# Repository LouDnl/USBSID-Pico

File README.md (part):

<br>
# 
USBSID-Pico is a RaspberryPi Pico/PicoW (RP2040) & Pico2/Pico2W (RP2350) based board for interfacing one or two MOS SID chips and/or hardware SID emulators over (WEB)USB with your computer, phone, ASID supporting player or USB midi controller.  

# This is USBSID-Pico! :)
| **“Raster Bar” (8-bit)** | **Van Halen's Jump<br>dual SID in Stereo!** | **Next Level** | **Outerversal<br>dual SID in Stereo!** |
|:-:|:-:|:-:|:-:|
| <br><small><sub>by LukHash</sub></small> | <br><small><sub>by Nordischsound</sub></small> | <br><small><sub>by Performers</sub> | <br><small><sub>by Abyxus</sub></small> |

| **Wonderland XI** | **Wonderland XII** | **Wonderland XIII** | **Wonderland XIV** |
|:-:|:-:|:-:|:-:|
| <br><small><sub>by Censor Design</sub></small> | <br><small><sub>by Censor Design</sub></small> | <br><small><sub>by Censor Design</sub> | <br><small><sub>by Censor Design</sub></small> |

# USBSID-Pro (Soon™)
In development is a modular USBSID-Pro featuring 4 SID sockets with 4 mono out ports, switchable audio channels into a single stereo out jack , Midi port, an onboard rp2350b and more. No release date has been planned yet!

# Index
* [This is USBSID-Pico! :)](#this-is-usbsid-pico-)
* [Swag!](#swag)
* [Software support & Features](#software-support-and-features)
  * [USBSID-Configtool](#usbsid-configtool)
  * [Software manual](doc/USBSID-Pico-software-manual.adoc) [PDF](doc/USBSID-Pico-software-manual.pdf)
  * [SID files](#sid-files)
    - [Webbased SID players](#webbased-sid-players)
    - [SID players](#sid-players)
    - [Amiga SID players](#amiga-sid-players)
  * [Commodore 64 emulators](#commodore-64-emulators)
  * [Chiptune trackers using SID's](#chiptune-trackers-using-sids)
  * [Driver code](#driver-code)
  * [Midi](#midi)
  * [Cynthcart VST](#cynthcart-vst)
* [Questions & Support](#questions-and-support)
* [Known issues](#known-issues)
* [Project status](#project-status)
  * [Code status](#code-status)
  * [Supported platforms](#supported-platforms)
  * [Linux Udev rules](#linux-udev-rules)
  * [Windows driver](#windows-driver)
* [Firmware](#firmware)
  * [Configuring your board's firmware](#configuring-your-boards-firmware)
    * [Testing your board](#testing-your-board)
  * [Firmware features](#firmware-features)
    * [Embedded Cynthcart](doc/USBSID-Pico-Cynthcart-manual.adoc) [(PDF)](doc/USBSID-Pico-Cynthcart-manual.pdf)
    * [Embedded USBSID-Player](doc/USBSID-Player-manual.adoc) [(PDF)](doc/USBSID-Player-manual.pdf)
  * [Firmware types and naming](doc/USBSID-Pico-firmware-manual.adoc) [(PDF)](doc/USBSID-Pico-firmware-manual.pdf)
  * [How to flash new firmware](doc/USBSID-Pico-firmware-manual.adoc) [(PDF)](doc/USBSID-Pico-firmware-manual.pdf)
  * [How to configure your board](doc/USBSID-Pico-firmware-manual.adoc) [(PDF)](doc/USBSID-Pico-firmware-manual.pdf)
  * [Building](#building)
* [Hardware](#hardware)
  * [Volume board](#volume-board)
  * [Where to buy](#where-to-buy)
  * [PCB usage information](#pcb-usage-information)
    * [PCB revision v1.0 manual](#pcb-revision-v10-manual)
    * [PCB revision v1.3 manual](#pcb-revision-v13-manual)
  * [Cases](#cases)
  * [PCB Features](#pcb-features)
  * [Open source design files, schematic and BOM](#open-source-design-files-schematic-and-bom)
  * [PCB Development](#pcb-development)
* [Examples](#examples)
* [Acknowledgements](#acknowledgements)
* [Disclaimer](#disclaimer)
* [License](#license)
* [Certification](#certification)

# Swag!
Do you like swag!? Yes please!! [greyandslate](https://bsky.app/profile/greyandslate.bsky.social) created these great t-shirt designs which are available for purchase in his [Smallrun shop](https://smallrun.net/shop/grey-and-slate-haberdashers), link below.  
**Use coupon code USBSID15 for a 15% discount!**  

# Software support and features
  
See the [Software manual](doc/USBSID-Pico-software-manual.adoc) for more information on how to use supported software!  

## USBSID-Configtool
The [USBSID-Configtool](https://github.com/LouDnl/USBSID-Configtool) is a _must have_ tool to configure your board!  
Checkout the [Configtool manual](doc/USBSID-Configtool-manual.adoc) or [PDF](doc/USBSID-Configtool-manual.pdf)  

## SID files
USBSID-Pico supports various ways of playing SID files.

#### Webbased SID players 
_Chrome webbrowser only_  
- Out-of-the box playing is supported by using [Deepsid by Chordian](https://deepsid.chordian.net)  
  by selecting `WebUSB (Hermit)` as player in the pulldown menu or  
  by selecting `ASID (MIDI)` as player in the pulldown menu.
- Out-of-the box playing is also supported by using [C64jukebox by Kenchis](https://haendel.ddns.net:8443/static/c64jukebox.vue), note that this is still in BETA.  

#### SID players
| Acid64 Pro | VSID(Vice) | (lib)sidplayfp | Phosphor |  
|:-:|:-:|:-:|:-:|  
|  |  |  |  |  
| version [4.4.0](https://acid64.com/download)<br>(Windows only) | version [3.10.0](https://github.com/VICE-Team/svn-mirror/releases/tag/3.10.0) | player [2.16](https://github.com/libsidplayfp/libsidplayfp/releases/tag/v2.16.0rc)<br>lib [2.16](https://github.com/libsidplayfp/sidplayfp/releases/tag/v2.16.0rc) | [any version](https://github.com/sandlbn/Phosphor/releases) |  
| up to 3 SIDs | up to 3 SIDs | up to 3 SIDs | up to 4 SIDs |  

Other:
- [SidBerry](https://github.com/LouDnl/SidBerry) is a command line SID file player for Linux & Windows with up to 4 SIDs supported (Windows version is buggy).
- [TrueSID](https://csdb.dk/release/?id=259243) TrueSID is a Python based graphical SID player which utilizes JSIDPlay2 and / or SidplayFp to play SID tunes  

#### Amiga SID players
Real SID's on the Amiga? Why yes!
- [erique](https://github.com/erique) and [koobo](https://github.com/koobo) have added support to [playsid](https://github.com/erique/playsid.library)  

## Commodore 64 emulators
Official support has been added to:  
| Vice | JSIDPlay2 | Denise |
|:-:|:-:|:-:|  
|  |  |  |  
| version [3.10.0](https://github.com/VICE-Team/svn-mirror/releases/tag/3.10.0) | version [4.13](https://sourceforge.net/projects/jsidplay2/files/jsidplay2/4.13/) | version [2.7](https://sourceforge.net/projects/deniseemu/) |  
| up to 4 SIDs in x64sc | up to 4 SIDs | up to 4 SIDs |  

Others:
- Unofficial support is added to a fork of [RetroDebugger](https://github.com/LouDnl/RetroDebugger), up to 4 SIDs are supported.

## Chiptune trackers using SID's
Into creating chiptunes? USBSID-Pico is your board!
- You should be able to use the ASID fork of [sidfactory2](https://github.com/Chordian/sidfactory2/tree/asid-support) without issues.  
- When using Vice or RetroDebugger you can freely use applications like [SID-Wizard](https://sourceforge.net/projects/sid-wizard/) for music creation.  
- There is also work being done in my forks of [GTUltra](https://github.com/LouDnl/GTUltra-USBSID) and [Goattracker2](https://github.com/LouDnl/goattracker2).  
  Ask on Discord for latest binaries :)

## Driver code
Want to create your own implementation? You can by using the driver code examples below
- [USBSID-Pico driver](https://github.com/LouDnl/USBSID-Pico-driver) repo is available @ https://github.com/LouDnl/USBSID-Pico-driver and contains `C++`, `Java` and `Javascript` implementation examples
  - [@sandlbn](https://github.com/sandlbn) has created a driver in `Rust` which is available as [USBSID-Pico-Rust-driver](https://github.com/sandlbn/USBSID-Pico-Rust-driver)
- [HardSID USB / SidBlaster USB](examples/hardsid-sidblaster) emulation driver example

## Midi
USBSID-Pico acts as Midi device and supports basic Midi in ~ note that Midi is still in development and in Beta phase.  
This means that no support is available here at this time, please visit the Discord for more information.

## Cynthcart VST
Raros has made a custom VST (Windows only) to use with the Cynthcart embedded firmware version.  
Checkout the [README.md](examples/Cynthcart-Ninja_VST/README.md) he made for more information!

# Questions and Support
Any questions about or support with USBSID-Pico can be asked 
* [Discord](https://discord.gg/zG2rxXuT2g)
* [Github discussions](https://github.com/LouDnl/USBSID-Pico/discussions)
* [USBSID manuals](doc/)

# Known issues
**PCB/Audio/etc**
* Possible audible low/high alternating hum when using a Pico1 or Pico2 board that has an RGB LED onboard.  
  - __Cause:__ Ground loop, when two or more interconnected pieces of audio equipment are plugged into different power outlets (with or without ground pins), creating multiple paths to the electrical ground.  
  - __Example:__ When powering the board from your computer and routing the audio out back into your computer.  
  - __Example:__ When powering the board from your computer and routing the audio out into speakers but both connected to different outlets.  
  - __Fix:__ Route the audio out through a ground loop isolator.  
  - __Fix:__ Connect audio out to headphones.  
  - __Note:__ Its more present on v1.0 and v1.3 board, but still there on v1.5 boards. To fix this on the board would require significant layout and pcb changes.  

**Firmware/Software**
* Switching on readmode and then switching it off again without restarting the PCB and Vice _can_ result in distorted audio  
* Highly demanding cycle-exact SID tunes (e.g. some digi/sample tunes) may not play at full speed on Pico1 or Pico1_w (RP2040) boards. Pico2 or Pico2_w (RP2350) is recommended for these tunes.  
* Crackles, clicks or short dropouts with highly demanding, cycle-exact SID tunes when the board is connected through a USB hub or a long/poor cable.  
  - __Cause:__ These tunes send thousands of small USB packets per second and the board only buffers a few writes. Hub type and speed, cable quality and other devices on the connection add delay.  
  - __Fix:__ Connect the board directly to a USB port of your computer.  
  - __Fix:__ When a hub is needed, use a powered USB 2.0 (480 Mbit/s) or newer hub, preferably multi-TT, no chained hubs, and a short, good quality data cable.  
  - __Note:__ See [USB connection: hubs and cables](doc/USBSID-Pico-software-manual.adoc#usb-connection) in the software manual.  

# Project status
Visit the [Project Page](https://github.com/users/LouDnl/projects/1) for an up-to-date list of things being worked on.
While in development any mentioned features, options, etc. are subject to change.  

### Code status
|          | Master             | Dev                    |
| -------  | :-----             | :-----                 |
| Release  | [![release][1]][A] | [![tag][2]][B]       |
| Build    | [![build][3]][C]   | [![build][4]][C]       |
| Commit   | [![commit][5]][D]  | [![commit][6]][E]      |
|          | **Other**          |
| Latest   | [![tag][7]][F]     | [![release][8]][G]     |
| Open     | [![issues][9]][H]  | [![discussions][10]][I] |
| Info     | [![license][11]][J] | [![language][12]][K]   |

[1]: https://img.shields.io/github/v/release/LouDnl/USBSID-Pico
[2]: https://img.shields.io/github/v/tag/LouDnl/USBSID-Pico
[3]: https://img.shields.io/github/actions/workflow/status/LouDnl/USBSID-Pico/build.yml?branch=master
[4]: https://img.shields.io/github/actions/workflow/status/LouDnl/USBSID-Pico/build.yml?branch=dev
[5]: https://shields.io/github/last-commit/LouDnl/USBSID-Pico/master
[6]: https://shields.io/github/last-commit/LouDnl/USBSID-Pico/dev
[7]: https://shields.io/github/v/tag/LouDnl/USBSID-Pico?sort=semver
[8]: https://shields.io/github/v/release/LouDnl/USBSID-Pico
[9]: https://shields.io/github/issues/LouDnl/USBSID-Pico
[10]: https://shields.io/github/discussions/LouDnl/USBSID-Pico
[11]: https://shields.io/github/license/LouDnl/USBSID-Pico
[12]: https://shields.io/github/languages/top/LouDnl/USBSID-Pico
[A]: https://github.com/LouDnl/USBSID-Pico/actions/workflows/release.yml
[B]: https://github.com/LouDnl/USBSID-Pico/actions/workflows/tagged_build.yml
[C]: https://github.com/LouDnl/USBSID-Pico/actions/workflows/build.yml
[D]: https://github.com/LouDnl/USBSID-Pico/commits/master/
[E]: https://github.com/LouDnl/USBSID-Pico/commits/dev/
[F]: https://github.com/LouDnl/USBSID-Pico/tags
[G]: https://github.com/LouDnl/USBSID-Pico/releases
[H]: https://github.com/LouDnl/USBSID-Pico/issues
[I]: https://github.com/LouDnl/USBSID-Pico/discussions
[J]: https://github.com/LouDnl/USBSID-Pico/blob/master/LICENSE
[K]: https://github.com/LouDnl/USBSID-Pico

### Supported platforms
See the [Software manual](doc/USBSID-Pico-software-manual.adoc) for driver installation and supported software information!  
_In development_  
Linux: Vice, JSidplay2, Denise, SidplayFp, RetroDebugger, SidBerry, USB Midi, WebUSB & ASID (in webbrowser) SID Play  
Windows: Vice, JSidplay2, Denise, SidBerry, USB Midi, WebUSB & ASID (in webbrowser) SID Play  
Android: USB Midi, WebUSB & ASID (in webbrowser) SID Play
Amiga: PlaySID library

#### Linux Udev rules
See the [Software manual](doc/USBSID-Pico-software-manual.adoc) for udev rule installation information!  
An example rule file can be found [here](examples/udev-rules/69-usbsid-permissions.rules).

#### Windows driver
See the [Software manual](doc/USBSID-Pico-software-manual.adoc) for driver installation information!

# Firmware
See the [releases page](https://github.com/LouDnl/USBSID-Pico/releases) for more information on what's changed and previous releases.  

**WARNING!** Whenever the embedded USBSID-Player or Cynthcart is used the Pico MCU is overclocked to 250MHz (rp2040 & rp2350). Passive cooling _might/could_ be needed.  

### Configuring your board's firmware
Use the new official [USBSID-Configtool](https://github.com/LouDnl/USBSID-Configtool) to configure your board.  
Downloads are available in the [releases](https://github.com/LouDnl/USBSID-Configtool/releases) section of the tools githubpage.  
Make sure you read the [Firmware manual](doc/USBSID-Pico-firmware-manual.adoc) for more information on how to set up your board!  

#### Testing your board
You can test your board with WebUSB and ASID here on the same site as the web configuration tool here: [USBSID web configuration tool](https://usbsid.loudai.nl/?player=webusb) (requires a Chrome based browser).  

### Firmware features
The firmware is still in development so features might change, be added or removed.
- By default both sockets are enabled and the configuration is set to 2 SID's.
- Custom CDC protocol for playing SID files or usage with emulators
- WebUSB support using the same CDC protocol for WebUSB supporting players
  - Play SID files in your browser via [Deepsid](https://deepsid.chordian.net/) by Chordian
  - Play SID files in your browser via [C64jukebox](https://haendel.ddns.net:8443/static/c64jukebox.vue) by Kenchis
- Dedicated WebSerial CDC interface for Windows, where WebUSB can crash the browser
- Midi (in) ASID support (heavily inspired by multiple sources)
  - Play SID files in your (midi supporting) browser via [Deepsid](https://deepsid.chordian.net/) by Chordian
  - Play SID files in your (midi supporting) browser via [IneSID](https://inesid.fazibear.me/) by Fazibear
- Midi device support over USB
  - Use your USBSID-Pico as Synth with your Midi controller
- Cynthcart embedded (special firmwares only)
  - Starting with firmware version v0.6.0-BETA and up some firmwares have Cynthcart as midi input  
    See the [USBSID-Pico Cynthcart manual](doc/USBSID-Pico-Cynthcart-manual.pdf) for more information!
- Embedded USBSID-Player for playing PSID, RSID, PRG or P00 files without a computer operated emulator!
  - Starting with firmware version v0.6.0-BETA and up some firmwares have USBSID-Player embedded  
    See the [USBSID-Player manual](doc/USBSID-Player-manual.pdf) for more information!
- Two SID sockets with up to 4 SID's (e.g. SKPico) supported
  - Socket one address range $00 ~ $7F (default $00 ~ $1F) auto based on configuration settings
  - Socket two address range $00 ~ $7F (default $40 ~ $7F) auto based on configuration settings
  - Configurable via [config-tool](examples/config-tool) for Linux and Windows
- Onboard LED acts as VU meter calculated by the voices of SID1 (Pico & Pico2 only)
- Onboard RGB LED acts as second VU meter calculated by the voices of SID1 (default)
  - Requires Black Pico clone board with RGB LED onboard!
  - SID voices to use for calculation can be changed in config
- Uses the [TinyUSB](https://github.com/hathach/tinyusb) stack
- Network SID Device (NSD) server over WiFi (`pico_w`/`pico2_w`)
  - Appears on the LAN and is auto-discovered by NSD clients such as ACID 64, JSidplay2 and SIDPlay
  - Configuration of SSID/PSK WIFI/Bluetooth enable via configtool
  - Plays cycle-exact SID streams on real hardware, USB stays fully functional
  - Bluetooth Classic SPP transport for the same protocol via a host-side bridge ([`examples/nsd_spp_bridge.py`](examples/nsd_spp_bridge.py)) for clients that only speak TCP
  - Speaks protocol version 5 (up to 16 SIDs and FM OPL), routed to the FM OPL socket when configured. `TRY_WRITE_EX` address `$DF40` is the FM OPL address port and `$DF50` the data port
  - Lets a v5 client enable or disable FM OPL on a SID socket remotely (same as the config tool), enabling a disabled FM OPL resets the chip
  - NSD enable and discovery settings apply live, WiFi state and IP address can be queried (`cfg_usbsid -wifis`)
- Optional SID register stream on a second vendor USB interface (build with `-DENABLE_SID_STREAM=1`), plus batch reads of up to 63 registers per USB packet
- USB RX ringbuffer (default on): up to 8 incoming USB packets are buffered and played from the main loop: a host USB scheduling delay no longer leaves the SID idle (no cracks on write-heavy tunes). Applies to CDC and WebUSB, rp2040 and rp2350, takes effect after a reboot
- Clock link (default off): mirror the SID clock to PHI2 for linking boards, or drive PHI1 from an external clock on PHI2; set with `cfg_usbsid -lclk` or the Configtool, the board saves and reboots on change
#### v1.3+ PCB
- Audio switch Stereo/Mono control
#### v1.5+ PCB
- Socket voltage control

### Building
You can build the firmware using the Pico SDK 2.1.1 and the included TinyUSB. Be sure to clone the SDK with `--recurse-submodules`.  
After download run `cd pico-sdk/lib/tinyusb` and then `python3 tools/get_deps.py PICO_PLATFORM` where PICO_PLATFORM is either rp2040 or rp2350 depending on the board you are using.

# Hardware

## Where to buy
#### My SmallRun store
You can purchase/pre-order (semi) assembled boards with or without Pico via my [SmallRun store](https://smallrun.net/shop/loud)!
**Run #1 is complete successfully:** [USBSID-Pico v1.5c Blue PCB](https://smallrun.net/shop/loud/usbsid-pico-v1-5c-blue-pcb).
  
<!-- Sponsored by  -->
#### PCBWay
At a minimum of 5 bare or assembled boards it is also possible to purchase PCB's at PCBWay  
No account yet at [PCBWay](https://pcbway.com/g/2458i7)? Please use [my referral link](https://pcbway.com/g/2458i7) to register, thanks!  
[Volume daughterboard](https://www.pcbway.com/project/shareproject/USBSID_Pico_Volume_daughterboard_5b782004.html)  
[PCB revision v1.5 (soon!)](#)  
[PCB revision v1.3](https://www.pcbway.com/project/shareproject/USBSID_Pico_v1_3_05f2b88e.html)  
[PCB revision v1.0](https://www.pcbway.com/project/shareproject/USBSID_Pico_c99c9748.html)  
#### Known and approved resellers
[Run Stop Re-Store](https://www.runstoprestore.nl) at [Retro8BITshop](https://www.retro8bitshop.com) is the first reseller to sell licensed USBSID-Pico boards.  
PCB revision v1.3 [product page](https://www.retro8bitshop.com/product/usbsid-pico-by-loud/)

## PCB usage information
Your USBSID-Pico PCB has several hardware features like jumpers and pins that require your attention. Click on the viewing method
### PCB revision v1.5 manual
- [Open online PCB v1.5 manual](doc/USBSID-Pico-PCBv1.5-manual.adoc)
- [Download PCB v1.5 PDF manual](doc/USBSID-Pico-PCBv1.5-manual.pdf)
### PCB revision v1.3 manual
- [Open online PCB v1.3 manual](doc/USBSID-Pico-PCBv1.3-manual.adoc)
- [Download PCB v1.3 PDF manual](doc/USBSID-Pico-PCBv1.3-manual.pdf)
### PCB revision v1.0 manual
- [Open online PCB v1.0 manual](doc/USBSID-Pico-PCBv1.0-manual.adoc)
- [Download PCB v1.0 PDF manual](doc/USBSID-Pico-PCBv1.0-manual.pdf)
### Volume board
An optional volume board to control left and right audio independently.  
- Plug and play compatible with v1.5+ boards.  
- Compatibale with v1.3 boards with a small modification to provide voltage.  
Checkout the [manual](doc/USBSID-Volume-daughterboard.adoc) or [PDF](doc/USBSID-Volume-daughterboard.pdf)  

_Yes! There are cats ;-)_  

## Cases
All USBSID-Pico community created cases are available in the [cases](cases/) directory, direct links below.  
_Cases for PCB revision v1.0:_
* [Cartridge case](cases/v1.0/spotUP) by [@spotUP](https://github.com/spotUP/)
* [boxy case](cases/v1.0/schorsch3000) by [@schorsch3000](https://github.com/schorsch3000/)

_Cases for PCB revision v1.3:_
* [spotUP Cartridge case revisited](cases/v1.3/spotUP-revisited) by [@LouD](https://github.com/LouDnl/)
* [Dual USBSID-Pico Commodore 64 Case](cases/v1.3/Dual_USBSID-Pico_Commodore_64_Case) by [@OlefinMakes](https://github.com/OlefinMakes/)

_Cases for PCB revision v1.5:_  
* [spotUp Cartridge case, LouD v1.5 remix](cases/v1.5/spotUp-LouD_remix) by [@LouD](https://github.com/LouDnl/)

## PCB Features
### volume board
- Control the volume of the left and right audio channel independently
### revision v1.5
- Improved voltage and audio filtering
  - Input voltage filtering with π LC filter
  - ESD protection diode on audio port for (minimal) backwards/reverse voltage protection
  - Extra filter capacitors on SID 5v and hv (9v/12v) voltage input
  - Softpull to gnd when headphone jack is empty (should help against clicks on jack insert)
- Jumperless design
  - Automatic 9v/12v selection based on detected Chip/SID
    - sockets are independently configuratble for 9v or 12
    - 5v and hv (9v/12v) on/off is for both sockets (sorry not enough gpios!)
  - Automatic per socket SID filter capacitor selection based on detected Chip/SID
  - Automatic per socket 6581 shunt resistor on/off based on detected Chip/SID
  - Automatic per socket 8580 digiboost based on detected Chip/SID
- Updated audio expansion pins
  - Plug and play ready for the new "Volume daughterboard"
  - Ext IN always connected 
    - Be carefull when connecting anything to this pin!
  - Includes SID voltage pin
- Includes all other features from v1.3
### revision v1.3
- Supports all MOS SID chips e.g. MOS6581, MOS6582 & MOS8580
- Supports SID chip replacements e.g. [SIDKick-Pico](https://github.com/frntc/SIDKick-pico), [ARMSID](https://www.nobomi.cz/8bit/armsid/index_en.php) & [FPGASID](https://www.fpgasid.de), [SwinSID](https://github.com/dmantione/swinsid).
- USBSID-Pico will by default generate a 1 MHz square wave using pio
  - other clock speeds are configurable
- IO controlled Stereo/Mono switch, can be set in config or toggled during play with supported players
  - SID1 audio left
  - SID2 audio right
- Powered via USB
  - Three separate voltage regulators for filtered voltages to the SIDS
  - 1x fixed 5 volts and 2x 9 volts or 12 volts
  - 5v stepup for clean 5v VCC to both SID chips
  - Supports mixed voltage! e.g. you can use one MOS6581 (12v) together with one MOS6582 (9v) or MOS8580 (9v)
  - 12v/9v jumper for each SID socket, defautls to 12v ~ inspired by SIDBlaster-Nano design
- Audio out filter as in the C64 schematics
  - With optional 6581 resistor, solder the 6581 jumper pad in each audio circuit for this.
- Optional EXT-IN pulldown resistor as filter bypass to reduce filter noise for Digiplay on 8580 SID's
- SID socket placement is more spread out for:
  - easier filter capacitor access
  - optional ZIF sockets
- Better IO port layout
  - Unused GPIO pins for optional future expansion boards
  - IO5 pins for quad SID configuration
  - Uart pins
  - SID Ext in pins (requires closing the solder jumper on the bottom)
  - Ground pin
- New soldermask art ;)
### revision v1.0
- Supports all MOS SID chips e.g. MOS6581, MOS6582 & MOS8580
- Supports SID chip replacements e.g. [SIDKick-Pico](https://github.com/frntc/SIDKick-pico), [SwinSID](https://github.com/dmantione/swinsid), ARMSID (untested), FPGASID (untested)
- 1 MHz oscillator (external optional, enabled via jumper pad)
  - if no external clock is detected USBSID-Pico will generate a 1 MHz square wave using pio
    - clock speed is configurable
  - if an external clock is detected will read the external clock signal
- Power via USB
  - 5v stepup for clean 5v VCC to both SID chips
  - 12v or 9v stepup for clean VDD to both SID chips
    - 12v/9v jumper, defautls to 12v ~ inspired by [SIDBlaster-Nano](https://codeberg.org/CBMretro/SIDBlaster-USB_Nano) design
- Audio out filter as in the [C64 schematics](https://www.zimmers.net/anonftp/pub/cbm/schematics/computers/c64/250469-rev.A-right.gif)
  - With optional 6581 resistor, solder the 6581 (mislabeled 8580!) jumper pad in each audio circuit for this.
- Audio jumper
  - SID1 audio left & right
  - SID1 audio left & SID2 audio right
- Optional EXT-IN pulldown resistor as filter bypass to reduce filter noise for Digiplay on 8580 SID's

## Open source design files, schematic and BOM
If you want and are up to it you can solder your own PCB or create your own development board using  
the open source KiCad design files and gerbers documents below.
#### revision v1.0
- [USBSID-Pico v1.0 schematic](hardware/v1.0-schematic.pdf)
- [USBSID-Pico v1.0 interactive BOM](https://htmlpreview.github.io/?https://github.com/LouDnl/USBSID-Pico/blob/master/hardware/v1.0-ibom.html)
- [USBSID-Pico v1.0 KiCad project & gerber files](hardware/USBSID-Pico-v1.0/README.md)
#### revision v1.3
- [USBSID-Pico v1.3 schematic](hardware/v1.3-schematic.pdf)
- [USBSID-Pico v1.3 interactive BOM](https://htmlpreview.github.io/?https://github.com/LouDnl/USBSID-Pico/blob/master/hardware/v1.3-ibom.html)
- [USBSID-Pico v1.3 KiCad project & gerber files](hardware/USBSID-Pico-v1.3/README.md) 
#### revision v1.5c
- [USBSID-Pico v1.5 schematic](hardware/v1.5c-schematic.pdf)
- [USBSID-Pico v1.5 interactive BOM](https://htmlpreview.github.io/?https://github.com/LouDnl/USBSID-Pico/blob/master/hardware/v1.5c-ibom.html)
#### volume-daughterboard v1.0
- [USBSID-Volume-daughterboard schematic](hardware/volume-daughterboard-schematic.pdf)
- [USBSID-Volume-daughterboard interactive BOM](https://htmlpreview.github.io/?https://github.com/LouDnl/USBSID-Pico/blob/master/hardware/volume-daughterboard-ibom.html)
- [USBSID-Volume-daughterboard KiCad project & gerber files](hardware/Volume-daughterboard/README.md) 
#### Datasheets of parts used
[Datasheets](resources/)

## PCB Development
* v1.5c **release** board<br>
    
* v1.5b _unreleased_ board<br>
    
* v1.5 _unreleased_ board<br>
    
* v1.4d _unreleased_ board<br>
    
* v1.4 _unreleased_ board<br>
    
* v1.3c _unreleased_ board<br>
    
* v1.3b **release** board<br>
    
* v1.2 _unreleased_ board<br>
    
* v1.1 _unreleased_, unfinished and skipped
* v1.0 **release** board<br>
    
* v0.2 _unreleased_ testboard<br>
    
* v0.1 _unreleased_ testboard<br>

# Examples
Visit my [Youtube channel](https://www.youtube.com/channel/UCOu1hPBTsEbG7ZFnk9-29KQ), [other socials](https://github.com/LouDnl) or the [SHOWCASE](SHOWCASE.md) page to see more examples of the board in action.

# Acknowledgements
Special thanks goes out to [@tobozo](https://github.com/tobozo/) for making the USBSID-Pico logo and for his (mental🤣) support since starting this project.  
Thanks to [@erique](https://github.com/erique) and [@koobo](https://github.com/koobo) for creating and implementing Amiga support!  
Thanks to [@Chordian](https://github.com/Chordian) for implementing my crappy webusb solution into deepsid.  
Thanks to [@kenchis](https://sourceforge.net/u/kenchis/profile/) for adding webusb support to jsidplay2's c64jukebox.  
Thanks to [PiCiJi](https://bitbucket.org/piciji/workspace/overview) for adding support to Denise.  

Some portions of this code and board are heavily inspired on projects by other great people.
Some of those projects are - in no particular order:
* [SIDKICK-pico by Frenetic](https://github.com/frntc/SIDKick-pico)
* [SIDBlaster USB Nano by CBMretro](https://codeberg.org/CBMretro/SIDBlaster-USB_Nano)
* [TherapSID by Twisted Electrons](https://github.com/twistedelectrons/TherapSID)
* [TeensyROM by Sensorium Embedded](https://github.com/SensoriumEmbedded/TeensyROM)
* [SID Factory II by Chordian](https://github.com/Chordian/sidfactory2)
* [Cynthcart by PaulSlocum](https://github.com/PaulSlocum/cynthcart)

# Disclaimer
I do this stuff in my free time for my enjoyment. Since I like to share my joy in creating this with everyone I try my best to provide a working PCB and Firmware. I am in no way an electronics engineer and can give __no guarantees__ that this stuff does not break or damage your hardware, computer, phone, or whatever you try to hook it up to. Be sure to take great care when inserting any real MOS SID chips into the board. While everything has been tested with real chips, this is in no way a guarantee that nothing could go wrong. Use of this board and firmware at your own risk! I am in no way responsible for your damaged hardware. That being said, have fun!

# License
### Software License ~ GNUv2
All code written by me in this repository is licensed under the terms of the GNU General Public License as published by the Free Software Foundation, version 2.
Any code in this repository that is not written by me automatically falls under the licensing conditions by the authors of said code as mentioned in the source code header.
For for more information about this license please read the LICENSE document in the root of the USBSID-Pico repository.

### USBSID-Pico v1.5 PCB Hardware License ~ CC BY-NC-ND 4.0
USBSID-Pico v1.5 PCB © 2026 by <a href="https://github.com/LouDnl">LouD</a> is licensed under <a href="https://creativecommons.org/licenses/by-nc-nd/4.0/">Creative Commons Attribution-NonCommercial-NoDerivatives 4.0 International</a>

### USBSID-Pico v1.3 PCB Hardware License ~ CC BY-SA 4.0
<a href="https://github.com/LouDnl/USBSID-Pico/tree/master/hardware/USBSID-Pico-v1.3">USBSID-Pico v1.3 PCB</a> © 2025-2026 by <a href="https://github.com/LouDnl">LouD</a> is licensed under <a href="https://creativecommons.org/licenses/by-sa/4.0/">Creative Commons Attribution-ShareAlike 4.0 International</a>  

### USBSID-Pico v1.0 PCB Hardware License ~ CC BY-SA 4.0
<a href="https://github.com/LouDnl/USBSID-Pico/tree/master/hardware/USBSID-Pico-v1.0">USBSID-Pico v1.0 PCB</a> © 2024-2026 by <a href="https://github.com/LouDnl">LouD</a> is licensed under <a href="https://creativecommons.org/licenses/by-sa/4.0/">Creative Commons Attribution-ShareAlike 4.0 International</a>  

### USBSID-Volume-daughterboard PCB Hardware License ~ CC BY-SA 4.0
Volume-daughterboard v1.0 PCB © 2026 by <a href="https://github.com/LouDnl">LouD</a> is licensed under <a href="https://creativecommons.org/licenses/by-sa/4.0/">Creative Commons Attribution-ShareAlike 4.0 International</a>  

# Certification
### USBSID-Pico v1.3 PCB OSHWA certification
  
[OSHW] NL000045 | Certified open source hardware | [oshwa.org/cert](https://certification.oshwa.org/nl000045.html)

### USBSID-Pico v1.0 PCB OSHWA certification
  
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
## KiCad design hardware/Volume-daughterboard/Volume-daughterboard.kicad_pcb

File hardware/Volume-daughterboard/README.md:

# USBSID-Volume-daughterboard PCB design files
This directory contains the open source KiCad design files for v1.0 of the USBSID-Volume-daughterboard pcb.

# Gerbers
The gerber files are in the [gerbers](gerbers/) directory.

# Disclaimer
I do this stuff in my free time for my enjoyment. Since I like to share my joy in creating this with everyone I try my best to provide a working PCB and Firmware. I am in no way an electronics engineer and can give __no guarantees__ that this stuff does not break or damage your hardware, computer, phone, or whatever you try to hook it up to. Be sure to take great care when inserting any real MOS SID chips into the board. While everything has been tested with real chips, this is in no way a guarantee that nothing could go wrong. Use of this board and firmware at your own risk! I am in no way responsible for your damaged hardware. That being said, have fun!

# License
### Software License ~ GNUv2
All code written by me in this repository is licensed under the terms of the GNU General Public License as published by the Free Software Foundation, version 2.
Any code in this repository that is not written by me automatically falls under the licensing conditions by the authors of said code as mentioned in the source code header.
For for more information about this license please read the LICENSE document in the root of the USBSID-Pico repository.
### USBSID-Volume-daughterboard PCB Hardware License ~ CC BY-SA 4.0
Volume-daughterboard v1.0 PCB © 2026 by <a href="https://github.com/LouDnl">LouD</a> is licensed under <a href="https://creativecommons.org/licenses/by-sa/4.0/">Creative Commons Attribution-ShareAlike 4.0 International</a>

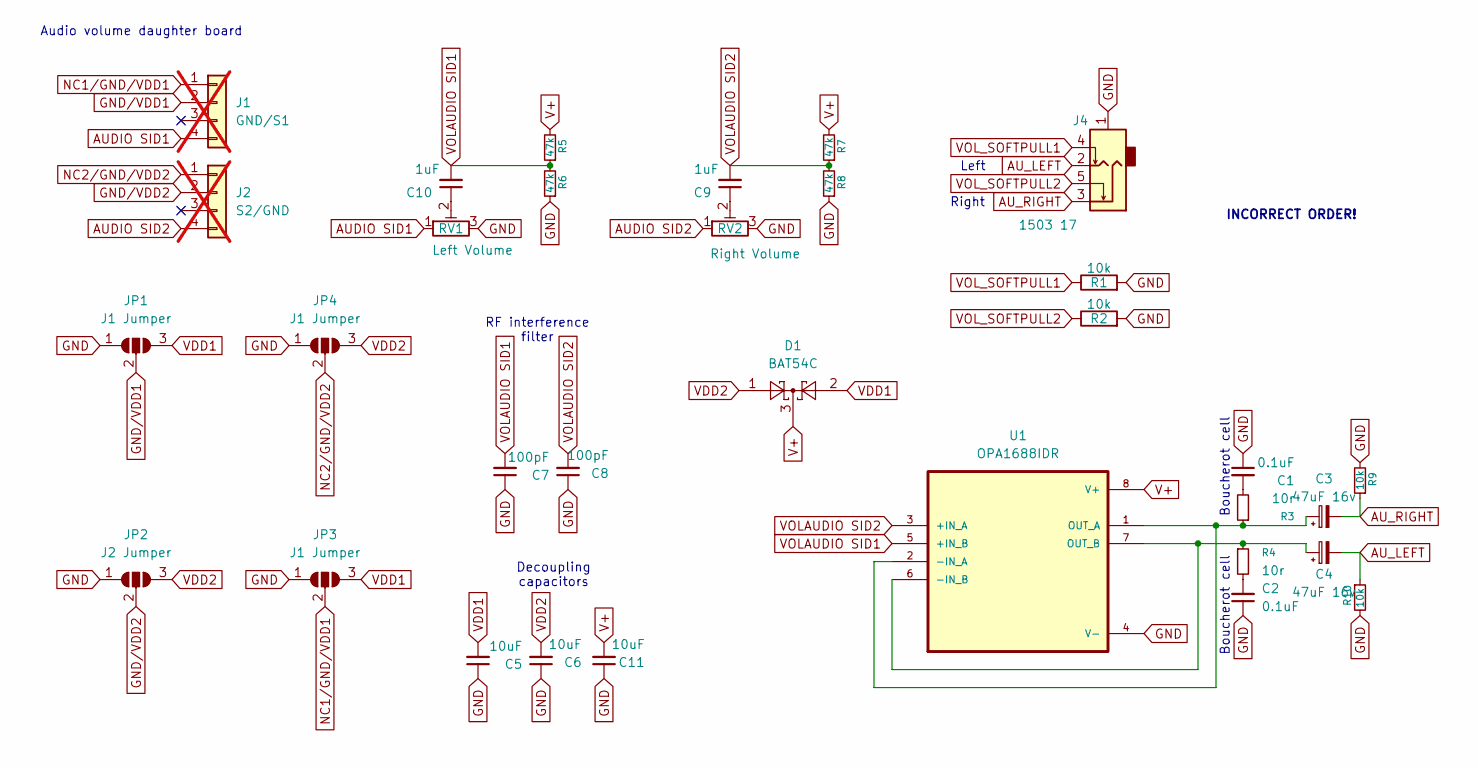
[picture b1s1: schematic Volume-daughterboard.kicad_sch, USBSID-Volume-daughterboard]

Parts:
C1, C2: 0.1uF; C_0805_2012Metric_Pad1.18x1.45mm_HandSolder
C3, C4: 47uF 16v; CP_Elec_5x5.4
C5, C6, C11: 10uF; C_0805_2012Metric_Pad1.18x1.45mm_HandSolder
C7, C8: 100pF; C_0805_2012Metric_Pad1.18x1.45mm_HandSolder
C9, C10: 1uF; C_0805_2012Metric_Pad1.18x1.45mm_HandSolder
D1: BAT54C; SOT-23; Mfg Part # BAT54C-7-F
J1: GND/S1; PinSocket_1x04_P2.54mm_Vertical; Mfg Part # PH2.54-01-04PZD; not fitted
J2: S2/GND; PinSocket_1x04_P2.54mm_Vertical; Mfg Part # PH2.54-01-04PZD; not fitted
J4: 1503 17; Lumberg 1503 17
JP1, JP3, JP4: J1 Jumper; SolderJumper-3_P1.3mm_Open_RoundedPad1.0x1.5mm
JP2: J2 Jumper; SolderJumper-3_P1.3mm_Open_RoundedPad1.0x1.5mm
R1, R2, R9, R10: 10k; R_0805_2012Metric; Mfg Part # 0805W8F1002T5E
R3, R4: 10r; R_0805_2012Metric
R5, R6, R7, R8: 47k; R_0805_2012Metric
RV1: Left Volume; PotentioMeter
RV2: Right Volume; PotentioMeter
U1: OPA1688IDR; SOIC127P599X175-8N; Mfg Part # OPA1688ID

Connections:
AUDIO SID1: J1.4, RV1.1
AUDIO SID2: J2.4, RV2.1
AU_LEFT: C4.2, J4.2, R10.1
AU_RIGHT: C3.2, J4.3, R9.1
GND: C1.1, C2.1, C5.1, C6.1, C7.1, C8.1, C11.1, J4.1, JP1.1 (A), JP2.1 (A), JP3.1 (A), JP4.1 (A), R1.2, R2.2, R6.1, R8.1, R9.2, R10.2, RV1.3, RV2.3, U1.4 (V-)
GND/VDD1: J1.2, JP1.2 (C)
GND/VDD2: J2.2, JP2.2 (C)
NC1/GND/VDD1: J1.1, JP3.2 (C)
NC2/GND/VDD2: J2.1, JP4.2 (C)
unnamed: C1.2, R3.2
unnamed: C2.2, R4.2
unnamed: C9.1, RV2.2
unnamed: C10.1, RV1.2
unnamed: C3.1, R3.1, U1.1 (OUT_A), U1.2 (-IN_A)
unnamed: C4.1, R4.1, U1.6 (-IN_B), U1.7 (OUT_B)
V+: C11.2, D1.3, R5.2, R7.2, U1.8 (V+)
VDD1: C5.2, D1.2, JP1.3 (B), JP3.3 (B)
VDD2: C6.2, D1.1, JP2.3 (B), JP4.3 (B)
VOLAUDIO SID1: C7.2, C10.2, R5.1, R6.2, U1.5 (+IN_B)
VOLAUDIO SID2: C8.2, C9.2, R7.1, R8.2, U1.3 (+IN_A)
VOL_SOFTPULL1: J4.4, R1.1
VOL_SOFTPULL2: J4.5, R2.1

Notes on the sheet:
Boucherot cell
Audio volume daughter board
RF interference filter
INCORRECT ORDER!
Left
Decoupling capacitors
Right

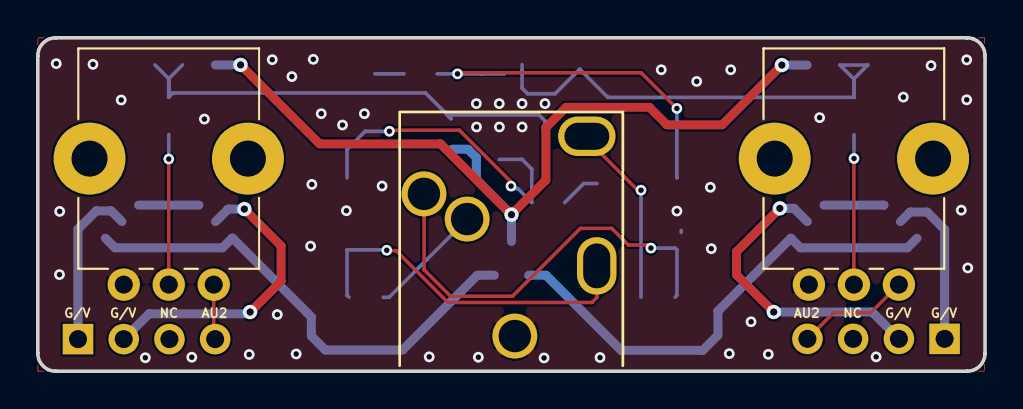
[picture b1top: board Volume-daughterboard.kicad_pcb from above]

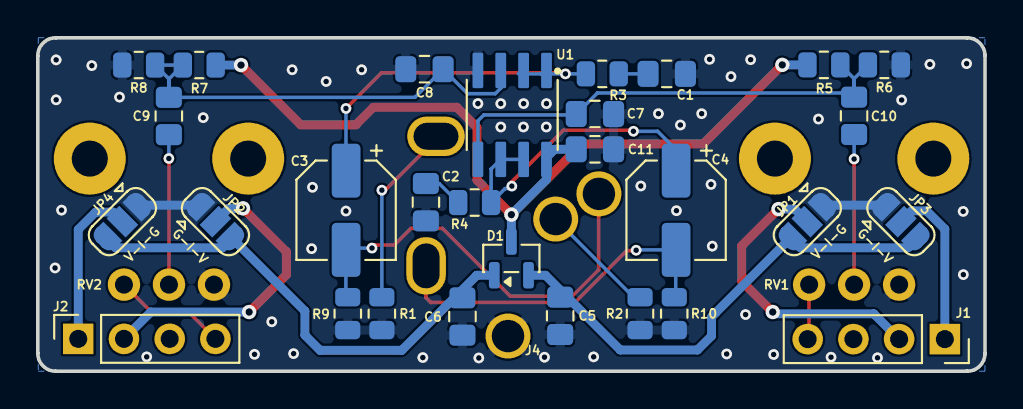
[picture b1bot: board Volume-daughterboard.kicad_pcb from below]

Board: 2 copper layers, 52.6 x 18.5 mm, 32 parts (29 on the bottom side), 22 nets.

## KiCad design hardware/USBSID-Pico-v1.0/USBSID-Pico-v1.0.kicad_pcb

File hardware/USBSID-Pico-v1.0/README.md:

# USBSID-Pico v1.0 PCB design files
This directory contains the open source KiCad design files for v1.0 of the USBSID-Pico pcb.  

# Gerbers
The gerber files are in the [gerbers](gerbers/) directory.

# OSHWA certification
  
[OSHW] NL000035 | Certified open source hardware | [oshwa.org/cert](https://certification.oshwa.org/nl000035.html)

# Disclaimer
I do this stuff in my free time for my enjoyment. Since I like to share my joy in creating this with everyone I try my best to provide a working PCB and Firmware. I am in no way an electronics engineer and can give __no guarantees__ that this stuff does not break or damage your hardware, computer, phone, or whatever you try to hook it up to. Be sure to take great care when inserting any real MOS SID chips into the board. While everything has been tested with real chips, this is in no way a guarantee that nothing could go wrong. Use of this board and firmware at your own risk! I am in no way responsible for your damaged hardware. That being said, have fun!

# License
### Software License ~ GNUv2
All code written by me in this repository is licensed under the terms of the GNU General Public License as published by the Free Software Foundation, version 2.
Any code in this repository that is not written by me automatically falls under the licensing conditions by the authors of said code as mentioned in the source code header.
For for more information about this license please read the LICENSE document in the root of the USBSID-Pico repository.
### USBSID-Pico v1.0 PCB Hardware License ~ CC BY-SA 4.0
<a href="https://github.com/LouDnl/USBSID-Pico/tree/master/hardware/USBSID-Pico-v1.0">USBSID-Pico v1.0 PCB</a> © 2024-2026 by <a href="https://github.com/LouDnl">LouD</a> is licensed under <a href="https://creativecommons.org/licenses/by-sa/4.0/">Creative Commons Attribution-ShareAlike 4.0 International</a>

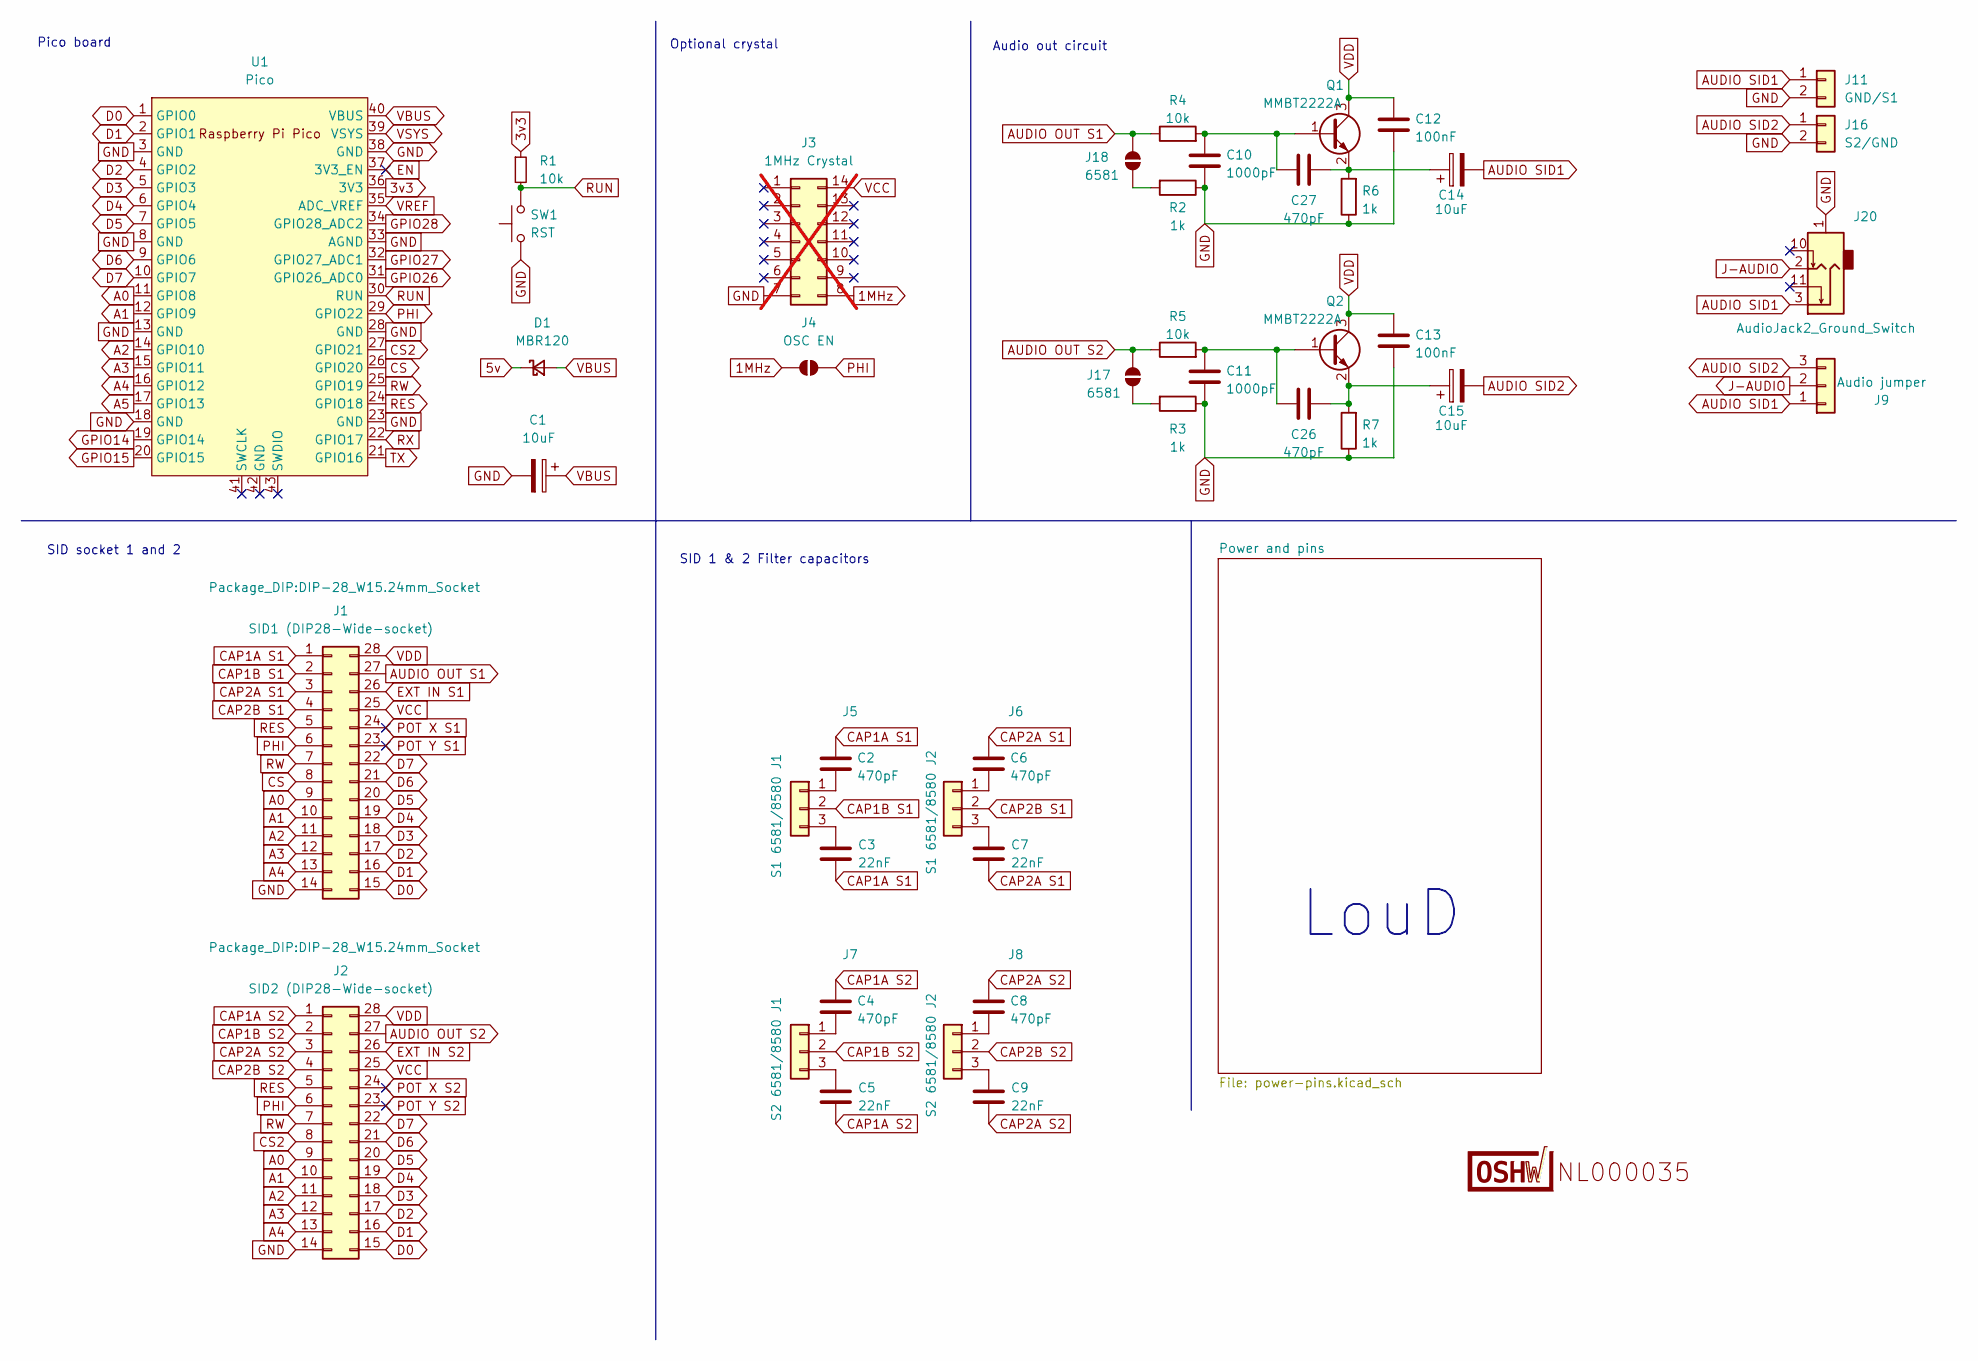
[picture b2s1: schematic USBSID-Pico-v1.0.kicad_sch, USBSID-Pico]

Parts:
C1: 10uF; CP_EIA-3216-10_Kemet-I_Pad1.58x1.35mm_HandSolder; Mfg Part # T491A106K016AT
C2, C4, C6, C8, C26, C27: 470pF; C_0805_2012Metric; Mfg Part # 0805B471K500NT
C3, C5, C7, C9: 22nF; C_0805_2012Metric; Mfg Part # CL21B223KBANNNC
C10, C11: 1000pF; C_0805_2012Metric; Mfg Part # CL21B102KBANNNC
C12, C13: 100nF; C_0805_2012Metric; Mfg Part # CL21B104KBCNNNC
C14, C15: 10uF; CP_Elec_4x5.3; Mfg Part # RVT1E100M0405
D1: MBR120; SOD-123FL_diode; Mfg Part # MBR120VLSFT1G
J1: SID1 (DIP28-Wide-socket); DIP-28_W15.24mm_Socket; Mfg Part # IC254V-12-28-0743-P1524
J2: SID2 (DIP28-Wide-socket); DIP-28_W15.24mm_Socket; Mfg Part # IC254V-12-28-0743-P1524
J3: 1MHz Crystal; DIP-14_W7.62mm; Mfg Part # MCO-1510A; not fitted
J4: OSC EN; SolderJumper-2_P1.3mm_Open_RoundedPad1.0x1.5mm
J5: S1 6581/8580 J1; PinHeader_1x03_P2.54mm_Vertical; Mfg Part # PH2.54-01-03PZD
J6: S1 6581/8580 J2; PinHeader_1x03_P2.54mm_Vertical; Mfg Part # PH2.54-01-03PZD
J7: S2 6581/8580 J1; PinHeader_1x03_P2.54mm_Vertical; Mfg Part # PH2.54-01-03PZD
J8: S2 6581/8580 J2; PinHeader_1x03_P2.54mm_Vertical; Mfg Part # PH2.54-01-03PZD
J9: Audio jumper; PinHeader_1x03_P2.54mm_Horizontal; Mfg Part # PH2.54-07-03PWD
J11: GND/S1; PinHeader_1x02_P2.54mm_Vertical; Mfg Part # PH2.54-01-02PZD
J16: S2/GND; PinHeader_1x02_P2.54mm_Vertical; Mfg Part # PH2.54-01-02PZD
J17, J18: 6581; SolderJumper-2_P1.3mm_Open_RoundedPad1.0x1.5mm
J20: AudioJack2_Ground_Switch; 3.5MM_SWITCHCRAFT_35RAPC4BHN2; Mfg Part # SJ1-3525N
LOGO1: (no value)
Q1, Q2: MMBT2222A; SOT-23; Mfg Part # MMBT2222ALT1G
R1, R4, R5: 10k; R_0805_2012Metric; Mfg Part # 0805W8F1002T5E
R2, R3, R6, R7: 1k; R_0805_2012Metric; Mfg Part # 0805W8F1001T5E
SW1: RST; SW_SPST_B3U-1000P_larger_pads; Mfg Part # B3U-1000P
U1: Pico; RPi_Pico_TH_PinRows_Only; Mfg Part # PM254-1-20-Z-8.5

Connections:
1MHz: J3.8, J4.2 (B)
3v3: R1.1, U1.36 (3V3)
5v: D1.1 (K); also elsewhere on the board
A0: J1.9, J2.9, U1.11 (GPIO8)
A1: J1.10, J2.10, U1.12 (GPIO9)
A2: J1.11, J2.11, U1.14 (GPIO10)
A3: J1.12, J2.12, U1.15 (GPIO11)
A4: J1.13, J2.13, U1.16 (GPIO12)
A5: U1.17 (GPIO13); also elsewhere on the board
AUDIO OUT S1: J1.27, J18.1 (A), R4.1
AUDIO OUT S2: J2.27, J17.1 (A), R5.1
AUDIO SID1: C14.2, J9.1, J11.1, J20.3
AUDIO SID2: C15.2, J9.3, J16.1
CAP1A S1: C2.2, C3.1, J1.1
CAP1A S2: C4.2, C5.1, J2.1
CAP1B S1: J1.2, J5.2
CAP1B S2: J2.2, J7.2
CAP2A S1: C6.2, C7.1, J1.3
CAP2A S2: C8.2, C9.1, J2.3
CAP2B S1: J1.4, J6.2
CAP2B S2: J2.4, J8.2
CS: J1.8, U1.26 (GPIO20)
CS2: J2.8, U1.27 (GPIO21)
D0: J1.15, J2.15, U1.1 (GPIO0)
D1: J1.16, J2.16, U1.2 (GPIO1)
D2: J1.17, J2.17, U1.4 (GPIO2)
D3: J1.18, J2.18, U1.5 (GPIO3)
D4: J1.19, J2.19, U1.6 (GPIO4)
D5: J1.20, J2.20, U1.7 (GPIO5)
D6: J1.21, J2.21, U1.9 (GPIO6)
D7: J1.22, J2.22, U1.10 (GPIO7)
EN: U1.37 (3V3_EN)
EXT IN S1: J1.26; also elsewhere on the board
EXT IN S2: J2.26; also elsewhere on the board
GND: C1.2, C10.2, C11.2, C12.2, C13.2, J1.14, J2.14, J3.7, J11.2, J16.2, J20.1, R2.1, R3.1, R6.1, R7.1, SW1.1, U1.3 (GND), U1.8 (GND), U1.13 (GND), U1.18 (GND), U1.23 (GND), U1.28 (GND), U1.33 (AGND), U1.38 (GND); also elsewhere on the board
GPIO14: U1.19 (GPIO14); also elsewhere on the board
GPIO15: U1.20 (GPIO15); also elsewhere on the board
GPIO26: U1.31 (GPIO26_ADC0); also elsewhere on the board
GPIO27: U1.32 (GPIO27_ADC1); also elsewhere on the board
GPIO28: U1.34 (GPIO28_ADC2); also elsewhere on the board
J-AUDIO: J9.2, J20.2
unnamed: C2.1, J5.1
unnamed: C3.2, J5.3
unnamed: C6.1, J6.1
unnamed: C7.2, J6.3
unnamed: C4.1, J7.1
unnamed: C5.2, J7.3
unnamed: C8.1, J8.1
unnamed: C9.2, J8.3
unnamed: J17.2 (B), R3.2
unnamed: J18.2 (B), R2.2
unnamed: C10.1, C27.2, Q1.1 (B), R4.2
unnamed: C14.1, C27.1, Q1.2 (E), R6.2
unnamed: C11.1, C26.2, Q2.1 (B), R5.2
unnamed: C15.1, C26.1, Q2.2 (E), R7.2
PHI: J1.6, J2.6, J4.1 (A), U1.29 (GPIO22)
POT X S1: J1.24
POT X S2: J2.24
POT Y S1: J1.23
POT Y S2: J2.23
RES: J1.5, J2.5, U1.24 (GPIO18)
RUN: R1.2, SW1.2, U1.30 (RUN)
RW: J1.7, J2.7, U1.25 (GPIO19)
RX: U1.22 (GPIO17); also elsewhere on the board
TX: U1.21 (GPIO16); also elsewhere on the board
VBUS: C1.1, D1.2 (A), U1.40 (VBUS)
VCC: J1.25, J2.25, J3.14; also elsewhere on the board
VDD: C12.1, C13.1, J1.28, J2.28, Q1.3 (C), Q2.3 (C); also elsewhere on the board
VREF: U1.35 (ADC_VREF)
VSYS: U1.39 (VSYS)

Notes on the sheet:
SID socket 1 and 2
SID 1 & 2 Filter capacitors
Pico board
Audio out circuit
LouD
Optional crystal

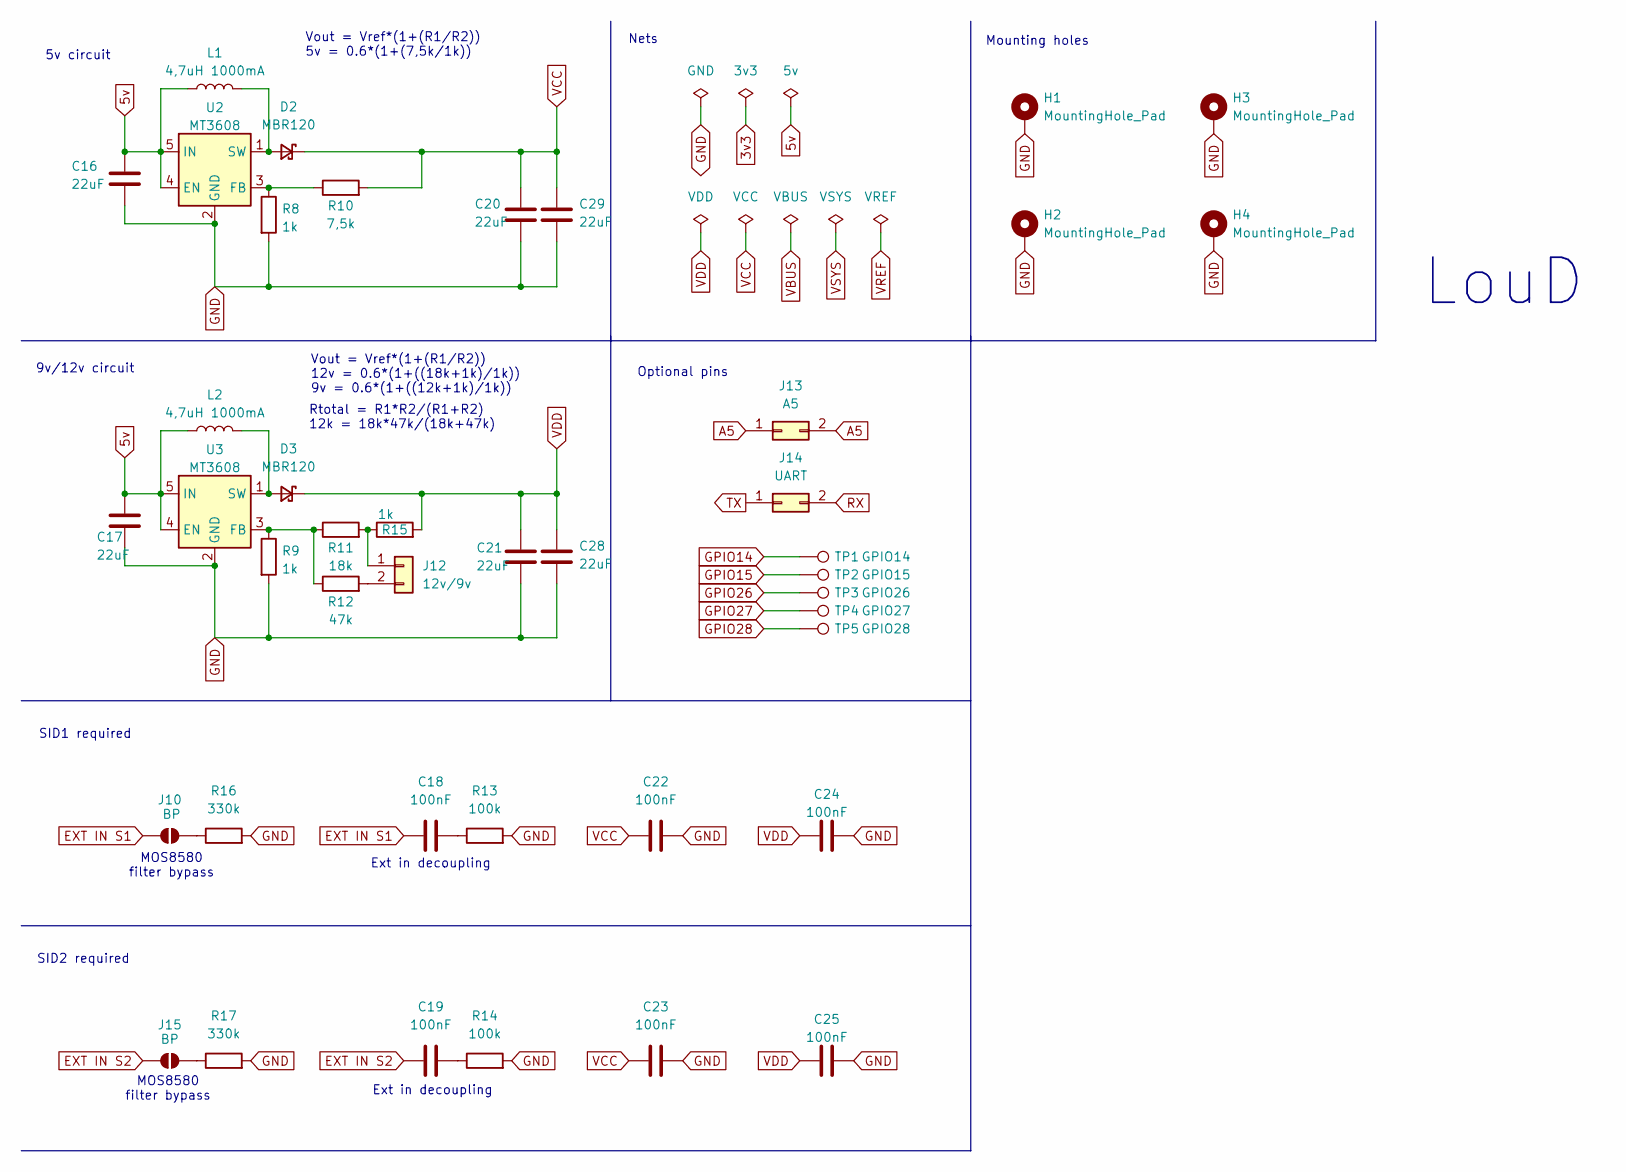
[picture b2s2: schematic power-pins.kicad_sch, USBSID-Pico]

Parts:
C16, C17, C20, C21, C28, C29: 22uF; C_0805_2012Metric; Mfg Part # CL21A226MAQNNNE
C18, C19, C22, C23, C24, C25: 100nF; C_0805_2012Metric; Mfg Part # CL21B104KBCNNNC
D2, D3: MBR120; SOD-123FL_diode; Mfg Part # MBR120VLSFT1G
H1, H2, H3, H4: MountingHole_Pad; MountingHole_3.2mm_M3_Pad_Via
J10, J15: BP; SolderJumper-2_P1.3mm_Open_RoundedPad1.0x1.5mm
J12: 12v/9v; PinHeader_1x02_P2.54mm_Vertical; Mfg Part # PH2.54-01-02PZD
J13: A5; PinHeader_2x01_P2.54mm_Vertical; Mfg Part # PH2.54-01-02PZD
J14: UART; PinHeader_1x02_P2.54mm_Vertical; Mfg Part # PH2.54-01-02PZD
L1, L2: 4,7uH 1000mA; L_1008_2520Metric_Pad1.43x2.20mm_HandSolder; Mfg Part # SPH252012H4R7MT
R8, R9, R15: 1k; R_0805_2012Metric; Mfg Part # 0805W8F1001T5E
R10: 7,5k; R_0805_2012Metric; Mfg Part # 0805W8F7501T5E
R11: 18k; R_0805_2012Metric; Mfg Part # 0805W8F1802T5E
R12: 47k; R_0805_2012Metric; Mfg Part # 0805W8F4702T5E
R13, R14: 100k; R_0805_2012Metric; Mfg Part # 0805W8F1003T5E
R16, R17: 330k; R_0805_2012Metric; Mfg Part # 0805W8F3303T5E
TP1: GPIO14; TestPoint_Pad_D1.0mm
TP2: GPIO15; TestPoint_Pad_D1.0mm
TP3: GPIO26; TestPoint_Pad_D1.0mm
TP4: GPIO27; TestPoint_Pad_D1.0mm
TP5: GPIO28; TestPoint_Pad_D1.0mm
U2, U3: MT3608; SOT-23-6; Mfg Part # MT3608

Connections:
5v: C16.1, C17.1, L1.1, L2.1, U2.4 (EN), U2.5 (IN), U3.4 (EN), U3.5 (IN); also elsewhere on the board
A5: J13.1, J13.2; also elsewhere on the board
EXT IN S1: C18.1, J10.2 (B); also elsewhere on the board
EXT IN S2: C19.1, J15.2 (B); also elsewhere on the board
GND: C16.2, C17.2, C20.2, C21.2, C22.2, C23.2, C24.1, C25.1, C28.2, C29.2, H1.1, H2.1, H3.1, H4.1, R8.2, R9.2, R13.2, R14.2, R16.2, R17.2, U2.2 (GND), U3.2 (GND); also elsewhere on the board
GPIO14: TP1.1; also elsewhere on the board
GPIO15: TP2.1; also elsewhere on the board
GPIO26: TP3.1; also elsewhere on the board
GPIO27: TP4.1; also elsewhere on the board
GPIO28: TP5.1; also elsewhere on the board
unnamed: C18.2, R13.1
unnamed: C19.2, R14.1
unnamed: D2.2 (A), L1.2, U2.1 (SW)
unnamed: D3.2 (A), L2.2, U3.1 (SW)
unnamed: J10.1 (A), R16.1
unnamed: J12.1, R11.2, R15.1
unnamed: J12.2, R12.2
unnamed: J15.1 (A), R17.1
unnamed: R8.1, R10.1, U2.3 (FB)
unnamed: R9.1, R11.1, R12.1, U3.3 (FB)
RX: J14.2; also elsewhere on the board
TX: J14.1; also elsewhere on the board
VCC: C20.1, C22.1, C23.1, C29.1, D2.1 (K), R10.2; also elsewhere on the board
VDD: C21.1, C24.2, C25.2, C28.1, D3.1 (K), R15.2; also elsewhere on the board

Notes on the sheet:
5v circuit
MOS8580 filter bypass
Optional pins
Nets
Rtotal = R1*R2/(R1+R2) 12k = 18k*47k/(18k+47k)
Mounting holes
9v/12v circuit
LouD
Ext in decoupling
Vout = Vref*(1+(R1/R2)) 5v = 0.6*(1+(7,5k/1k))
Vout = Vref*(1+(R1/R2)) 12v = 0.6*(1+((18k+1k)/1k)) 9v = 0.6*(1+((12k+1k)/1k))
SID2 required
SID1 required

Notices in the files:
README.md:
USBSID-Pico v1.5 PCB Hardware License ~ CC BY-NC-ND 4.0:
USBSID-Pico v1.5 PCB © 2026 by LouD is licensed under Creative Commons Attribution-NonCommercial-NoDerivatives 4.0 International
